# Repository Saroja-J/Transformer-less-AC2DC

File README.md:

# ⚡ Transformerless Power Supply

> A compact AC-to-DC power supply designed without using a bulky transformer. This project converts AC mains into a regulated low-voltage DC output using a capacitive dropper circuit, bridge rectifier, filter capacitors, and voltage regulator.

---

## 📌 Overview

This project demonstrates the design and simulation of a **Transformerless Power Supply** using **KiCad**. Instead of a conventional transformer, it uses a **capacitive dropper** to reduce the AC voltage, making the circuit lightweight, low-cost, and compact for low-power applications.

The output is regulated using a voltage regulator IC to provide a stable DC voltage suitable for electronic circuits.

---

## ⚙️ Working 

1.  **AC Input**
   - AC mains is applied to the input.

2.  **Capacitive Voltage Drop**
   - An X-rated capacitor limits the current without dissipating much power.

4.  **Rectification**
   - A bridge rectifier converts AC into pulsating DC.

6.  **Voltage Regulation**
   - A voltage regulator IC(7805) provides a stable DC output.

7.  **Output**
   - Clean regulated DC is available for low-power electronic devices.

---

## ✨ Features

 ✅ Transformerless compact design
 
 ✅ Low-cost implementation
 
 ✅ Bridge rectifier for AC-DC conversion
 
 ✅ Filter capacitors for ripple reduction
 
 ✅ Regulated DC output
 
 ✅ KiCad schematic design
 
 ✅ Suitable for low-power embedded applications

---

## 🛠 Components Used
- Input connector
- Capacitive Dropper Capacitor(225k/2.2uf)
- Bridge Rectifier (1N4007 Diodes)
- Filter Capacitors
- Current Limiting Resistors
- Voltage Regulator IC(LM7805)
- LED Indicator
- Output Connector

---

## 🚀 Applications

-  IoT Devices
-  Sensor Modules
-  LED Indicator Circuits
-  Home Automation
-  Low-Power Embedded Systems
-  Electronic Learning Projects

---

## ⚠️ Safety Warning

> **DANGER: HIGH VOLTAGE**

This circuit is **NOT electrically isolated** from the AC mains.

1 Do **NOT** touch any part of the circuit while powered.

2 Use only for educational, simulation, or properly enclosed applications.

3 Always disconnect power before testing or modifying the circuit.

4 Not recommended for beginners without proper supervision.

---

## 💻 Software Used

- 🟢 KiCad (10.0.1)

---

## 📷 Project Preview

---

## 📄 License

This project is intended for **educational and learning purposes**.

---

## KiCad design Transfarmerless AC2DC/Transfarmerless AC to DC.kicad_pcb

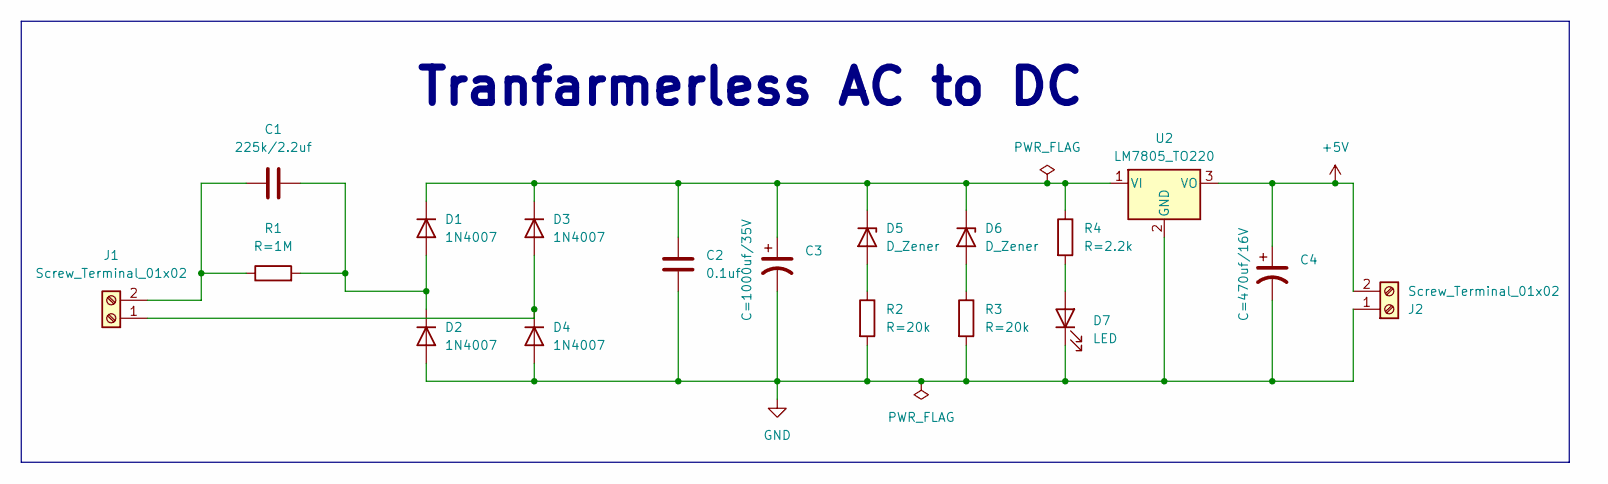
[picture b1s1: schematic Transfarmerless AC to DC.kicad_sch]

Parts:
C1: 225k/2.2uf; C_Rect_L18.0mm_W6.0mm_P15.00mm_FKS3_FKP3
C2: 0.1uf; C_Disc_D4.7mm_W2.5mm_P5.00mm
C3: C=1000uf/35V; CP_Radial_D10.0mm_P5.00mm
C4: C=470uf/16V; CP_Radial_D8.0mm_P3.50mm
D1, D2, D3, D4: 1N4007; D_DO-41_SOD81_P10.16mm_Horizontal
D5, D6: D_Zener; D_A-405_P7.62mm_Horizontal
D7: LED; LED_D5.0mm
J1, J2: Screw_Terminal_01x02; TerminalBlock_Phoenix_MKDS-1,5-2-5.08_1x02_P5.08mm_Horizont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
R1: R=1M; R_Axial_DIN0207_L6.3mm_D2.5mm_P7.62mm_Horizontal
R2, R3: R=20k; R_Axial_DIN0207_L6.3mm_D2.5mm_P7.62mm_Horizontal
R4: R=2.2k; R_Axial_DIN0207_L6.3mm_D2.5mm_P7.62mm_Horizontal
U2: LM7805_TO220; TO-220-3_Vertical

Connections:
+5V: C4.1, J2.2, U2.3 (VO)
GND: C2.2, C3.2, C4.2, D2.2 (A), D4.2 (A), D7.1 (K), J2.1, R2.2, R3.2, U2.2 (GND)
unnamed: C1.2, D1.2 (A), D2.1 (K), R1.2
unnamed: C2.1, C3.1, D1.1 (K), D3.1 (K), D5.1 (K), D6.1 (K), R4.1, U2.1 (VI)
unnamed: D3.2 (A), D4.1 (K), J1.1
unnamed: D5.2 (A), R2.1
unnamed: D6.2 (A), R3.1
unnamed: D7.2 (A), R4.2
unnamed: C1.1, J1.2, R1.1

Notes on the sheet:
Tranfarmerless AC to DC

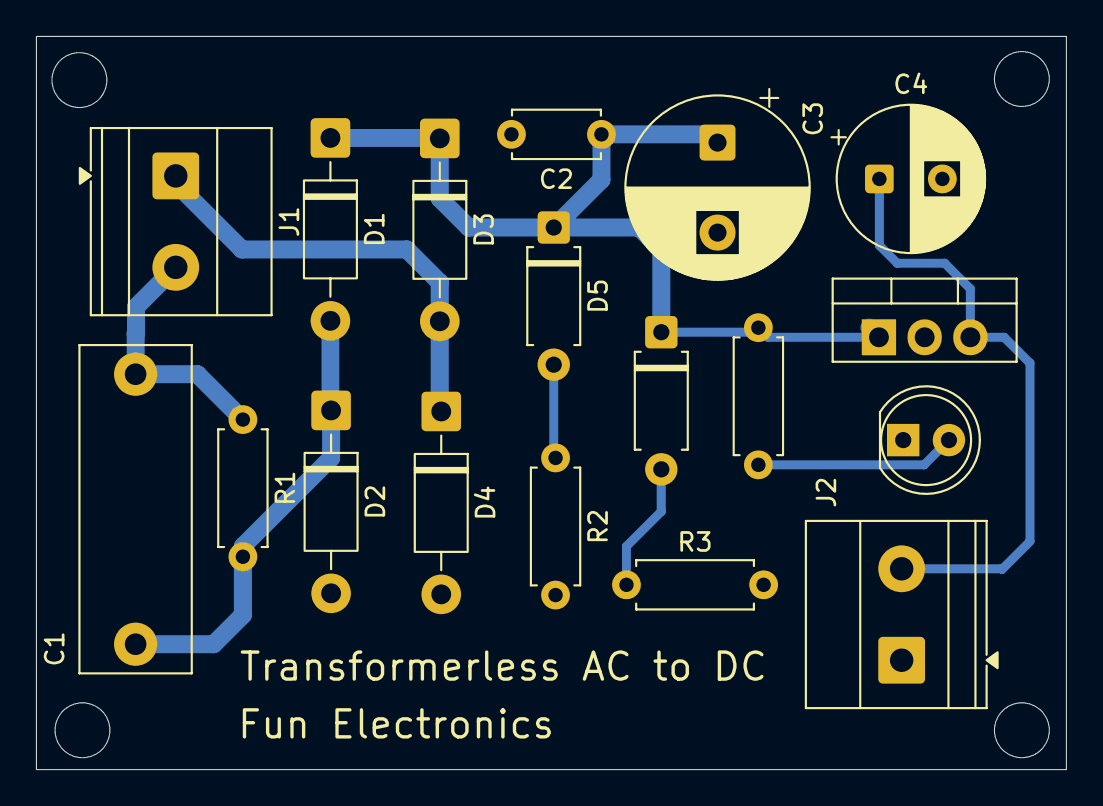
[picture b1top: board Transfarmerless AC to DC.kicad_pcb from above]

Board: 2 copper layers, 57.2 x 40.7 mm, 18 parts (0 on the bottom side), 9 nets.
